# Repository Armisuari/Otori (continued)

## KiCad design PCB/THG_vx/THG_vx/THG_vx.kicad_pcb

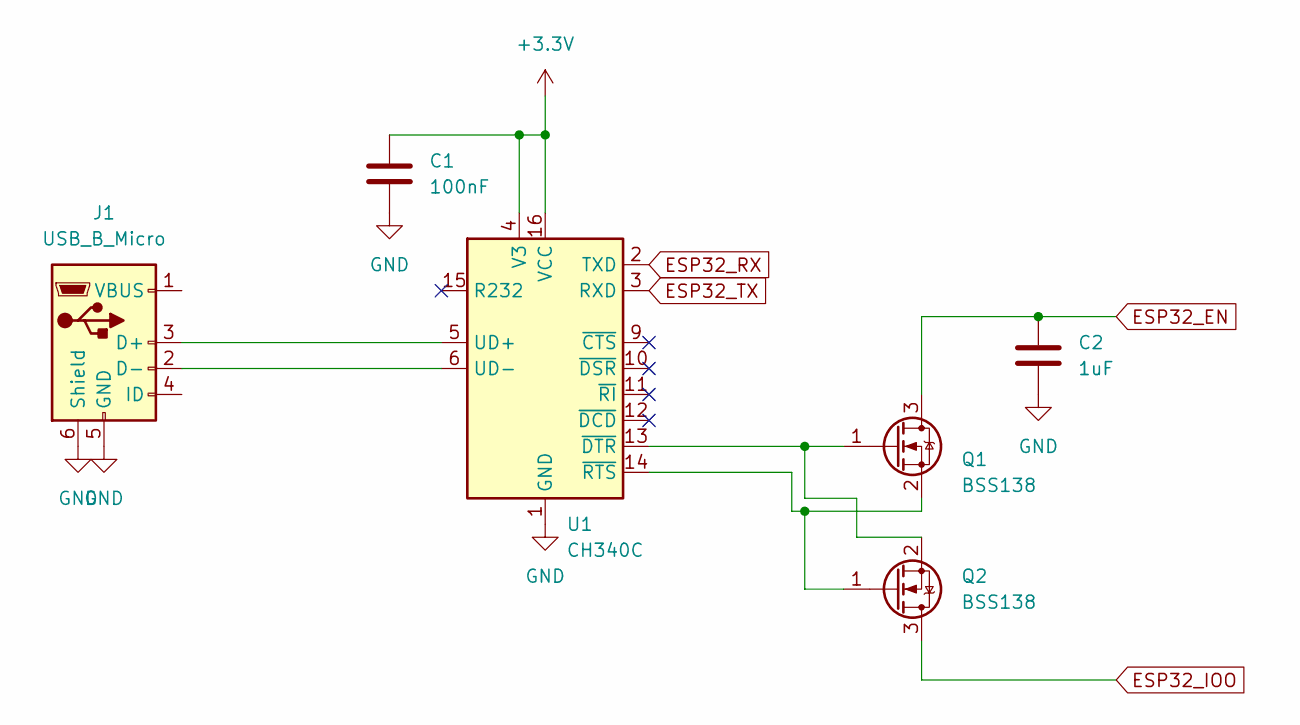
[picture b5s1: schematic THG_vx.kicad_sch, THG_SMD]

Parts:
C1: 100nF; C_0805_2012Metric
C2: 1uF; C_0805_2012Metric
J1: USB_B_Micro; USB_Micro-AB_Molex_47590-0001
Q1, Q2: BSS138; SOT-23
U1: CH340C; SOIC-16_3.9x9.9mm_P1.27mm

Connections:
+3V3: C1.1, U1.4 (V3), U1.16 (VCC)
ESP32_EN: C2.1, Q1.3 (D)
ESP32_IOO: Q2.3 (D)
ESP32_RX: U1.2 (TXD)
ESP32_TX: U1.3 (RXD)
GND: C1.2, C2.2, J1.5 (GND), J1.6 (Shield), U1.1 (GND)
unnamed: J1.3 (D+), U1.5 (UD+)
unnamed: J1.2 (D-), U1.6 (UD-)
unnamed: Q1.1 (G), Q2.2 (S), U1.13 (~DTR)
unnamed: Q1.2 (S), Q2.1 (G), U1.14 (~RTS)

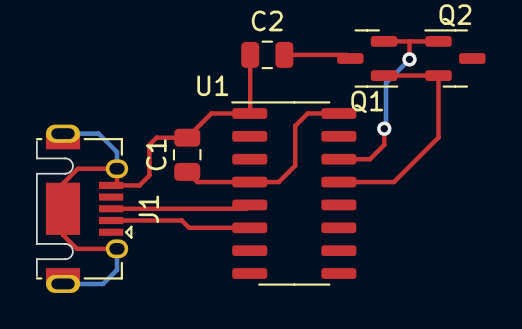
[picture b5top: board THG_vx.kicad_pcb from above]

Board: 2 copper layers, 6 parts (0 on the bottom side), 7 nets.

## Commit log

2022-03-10 adding previous gerber file
2022-03-10 adding pcb pic
2022-03-10 fix cordinate
2022-03-14 revisi
2022-03-14 Revisi 2
2022-03-14 revisi 3
2022-03-17 revisi tata letak dan rangkaian button
2022-07-21 push for the first-time
2022-07-21 generate gerber file of modbus rev2
